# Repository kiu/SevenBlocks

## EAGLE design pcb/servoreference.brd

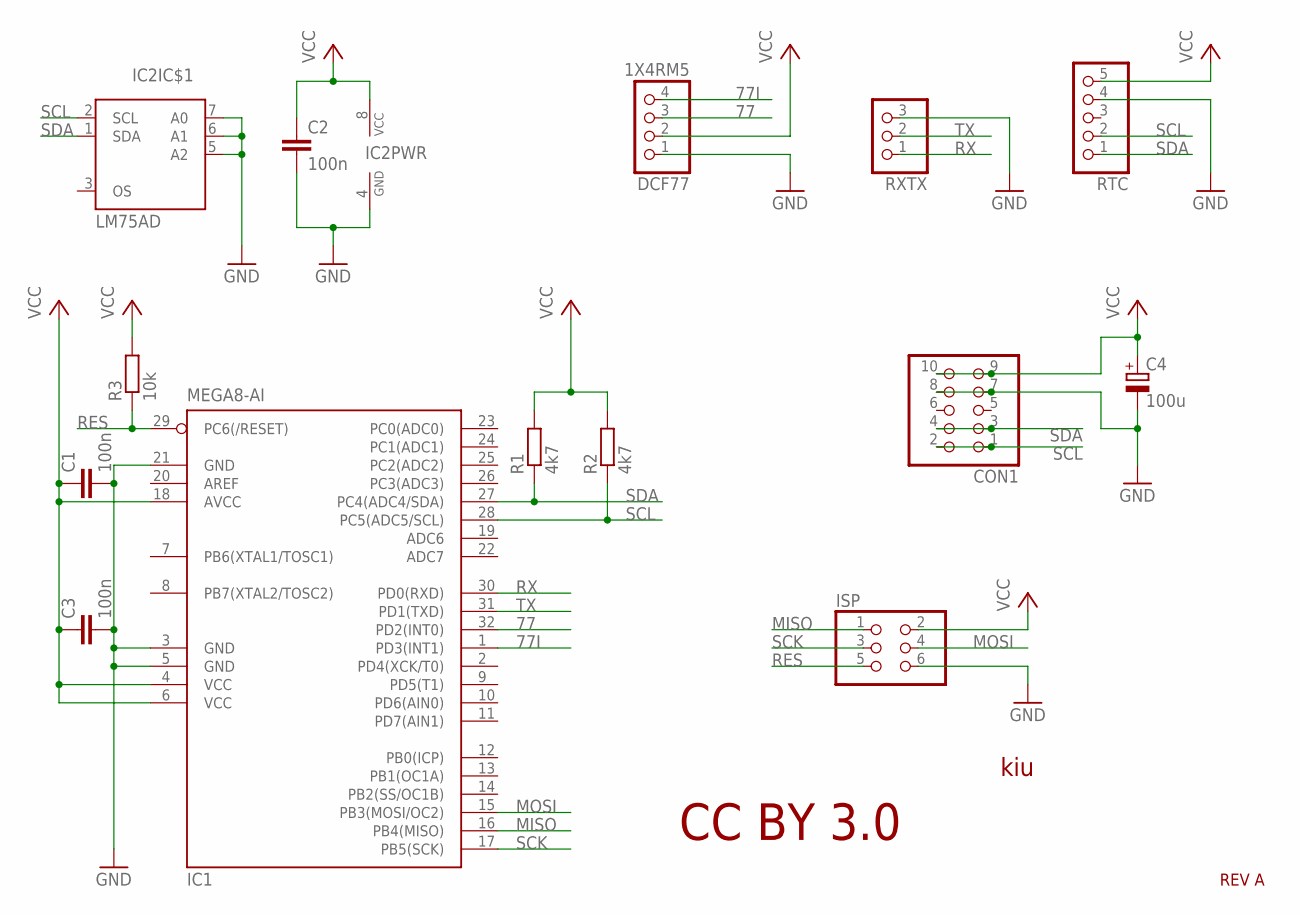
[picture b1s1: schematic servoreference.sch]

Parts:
C1, C2, C3: 100n; C0805
C4: 100u; 153CLV-0505
CON1: PINHD-2X5; 2X05
DCF77: 1X4RM5
IC1: MEGA8-AI; TQFP32-08; MPN ATMEGA8-16AU
IC2: LM75AD; SO08
ISP: PINHD-2X3; 2X03
R1, R2: 4k7; R0805
R3: 10k; R0805
RTC: PINHD-1X5; 1X05
RXTX: PINHD-1X3; 1X03

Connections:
77: DCF77.3, IC1.32 (PD2(INT0))
77I: DCF77.4, IC1.1 (PD3(INT1))
GND: C1.2, C2.2, C3.2, C4.-, CON1.7, CON1.8, DCF77.1, IC1.3 (GND), IC1.5 (GND), IC1.21 (GND), IC2.4 (GND), IC2.5 (A2), IC2.6 (A1), IC2.7 (A0), ISP.6, RTC.4, RXTX.3
MISO: IC1.16 (PB4(MISO)), ISP.1
MOSI: IC1.15 (PB3(MOSI/OC2)), ISP.4
RES: IC1.29 (PC6(/RESET)), ISP.5, R3.1
RX: IC1.30 (PD0(RXD)), RXTX.1
SCK: IC1.17 (PB5(SCK)), ISP.3
SCL: CON1.1, CON1.2, IC1.28 (PC5(ADC5/SCL)), IC2.2 (SCL), R2.1, RTC.2
SDA: CON1.3, CON1.4, IC1.27 (PC4(ADC4/SDA)), IC2.1 (SDA), R1.1, RTC.1
TX: IC1.31 (PD1(TXD)), RXTX.2
VCC: C1.1, C2.1, C3.1, C4.+, CON1.9, CON1.10, DCF77.2, IC1.4 (VCC), IC1.6 (VCC), IC1.18 (AVCC), IC2.8 (VCC), ISP.2, R1.2, R2.2, R3.2, RTC.5

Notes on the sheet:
CC BY 3.0
kiu
REV A

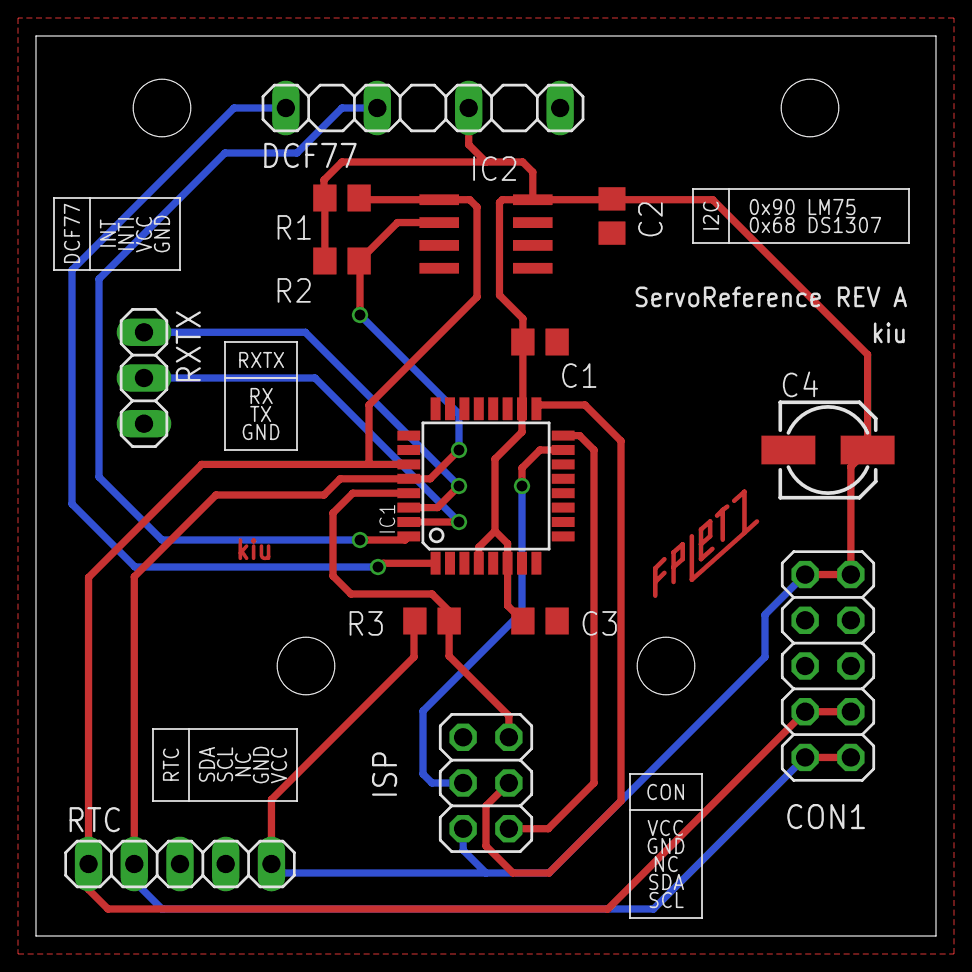
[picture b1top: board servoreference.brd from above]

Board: 2 copper layers, 50.0 x 50.0 mm, 14 parts (0 on the bottom side), 12 nets.

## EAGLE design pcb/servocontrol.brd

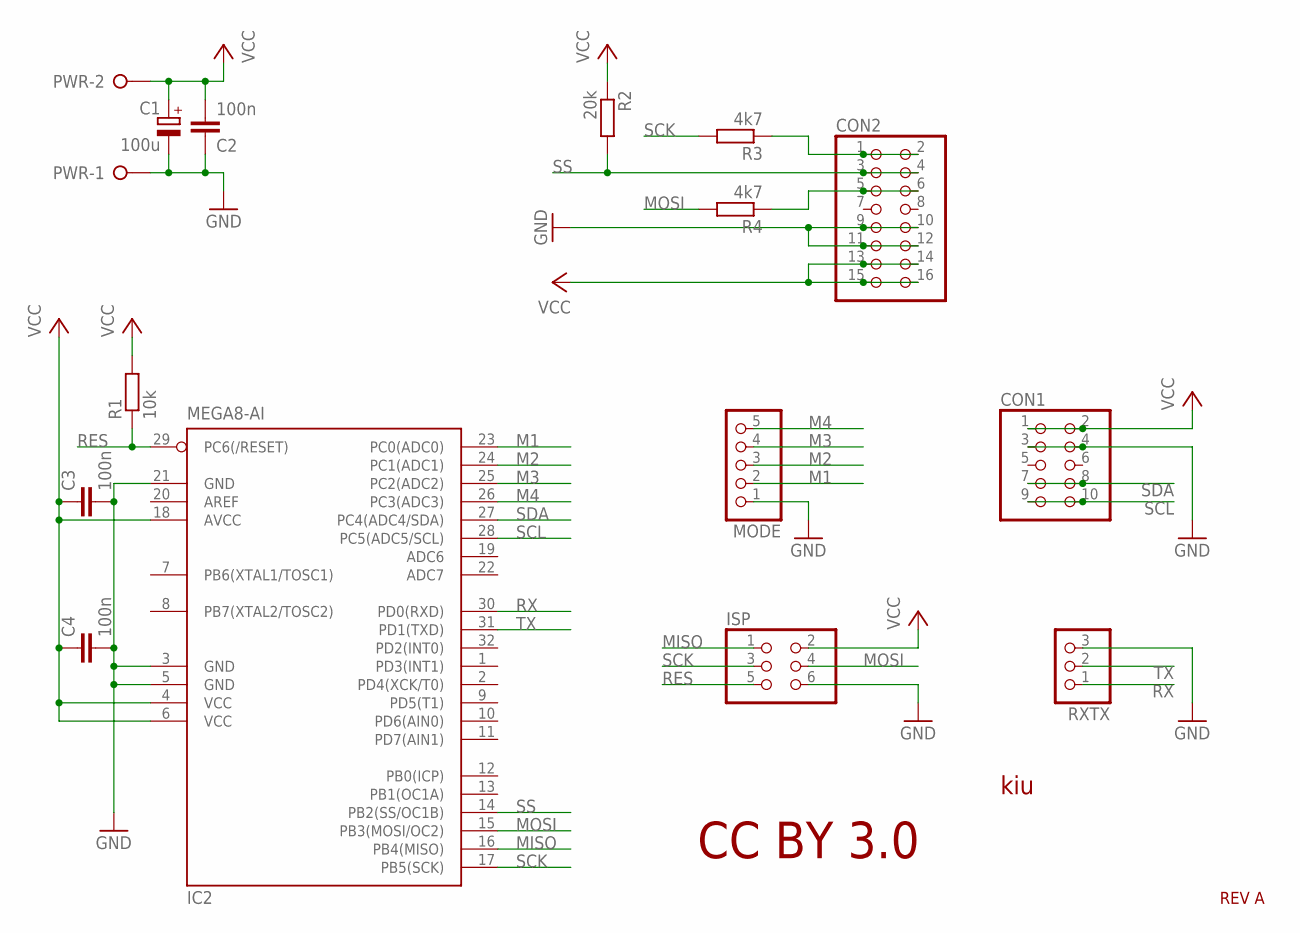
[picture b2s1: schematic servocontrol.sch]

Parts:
C1: 100u; 153CLV-0505
C2, C3, C4: 100n; C0805
CON1: PINHD-2X5; 2X05
CON2: PINHD-2X8; 2X08
IC2: MEGA8-AI; TQFP32-08; MPN ATMEGA8-16AU
ISP: PINHD-2X3; 2X03
MODE: PINHD-1X5; 1X05
PWR: W237-02P; W237-132
R1: 10k; R0805
R2: 20k; R0805
R3, R4: 4k7; R0805
RXTX: PINHD-1X3; 1X03

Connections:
GND: C1.-, C2.1, C3.2, C4.2, CON1.3, CON1.4, CON2.9, CON2.10, CON2.11, CON2.12, IC2.3 (GND), IC2.5 (GND), IC2.21 (GND), ISP.6, MODE.1, PWR.1, RXTX.3
M1: IC2.23 (PC0(ADC0)), MODE.2
M2: IC2.24 (PC1(ADC1)), MODE.3
M3: IC2.25 (PC2(ADC2)), MODE.4
M4: IC2.26 (PC3(ADC3)), MODE.5
MISO: IC2.16 (PB4(MISO)), ISP.1
MOSI: IC2.15 (PB3(MOSI/OC2)), ISP.4, R4.2
unnamed: CON2.5, CON2.6, R4.1
unnamed: CON2.1, CON2.2, R3.1
RES: IC2.29 (PC6(/RESET)), ISP.5, R1.1
RX: IC2.30 (PD0(RXD)), RXTX.1
SCK: IC2.17 (PB5(SCK)), ISP.3, R3.2
SCL: CON1.9, CON1.10, IC2.28 (PC5(ADC5/SCL))
SDA: CON1.7, CON1.8, IC2.27 (PC4(ADC4/SDA))
SS: CON2.3, CON2.4, IC2.14 (PB2(SS/OC1B)), R2.2
TX: IC2.31 (PD1(TXD)), RXTX.2
VCC: C1.+, C2.2, C3.1, C4.1, CON1.1, CON1.2, CON2.13, CON2.14, CON2.15, CON2.16, IC2.4 (VCC), IC2.6 (VCC), IC2.18 (AVCC), ISP.2, PWR.2, R1.2, R2.1

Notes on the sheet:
CC BY 3.0
kiu
REV A

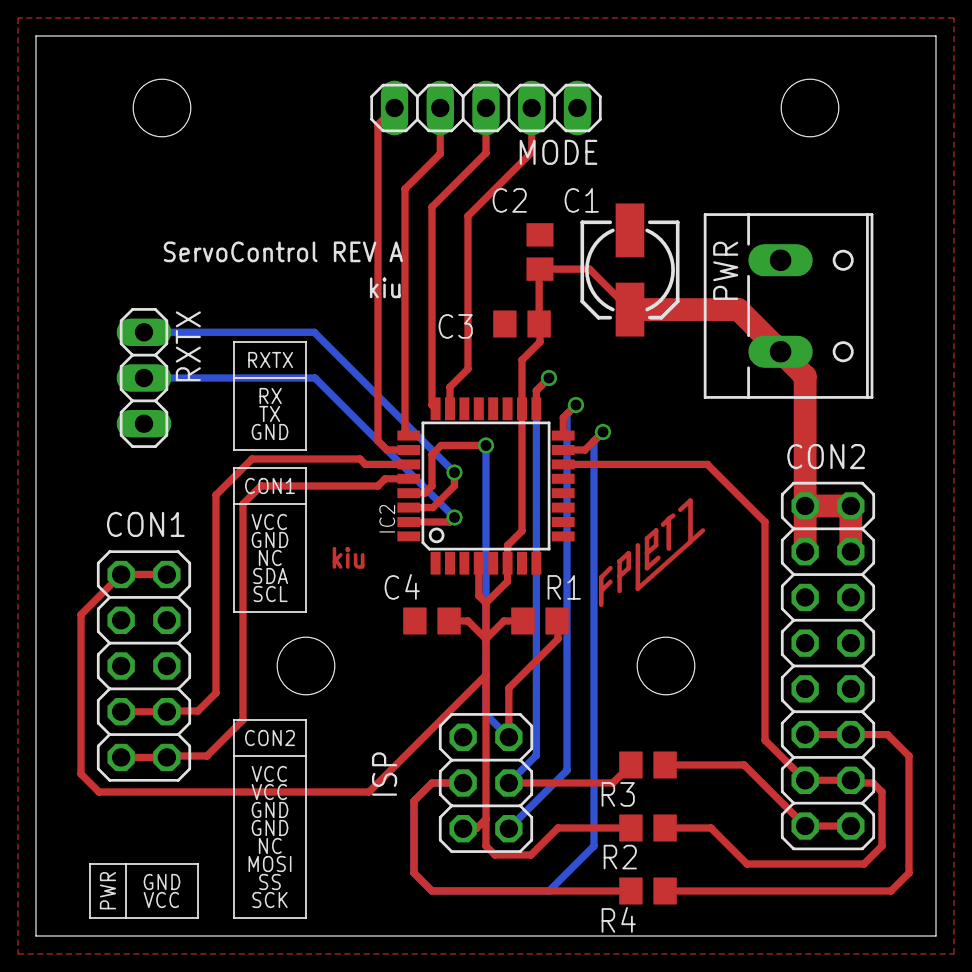
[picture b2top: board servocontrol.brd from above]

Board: 2 copper layers, 50.0 x 50.0 mm, 15 parts (0 on the bottom side), 17 nets.

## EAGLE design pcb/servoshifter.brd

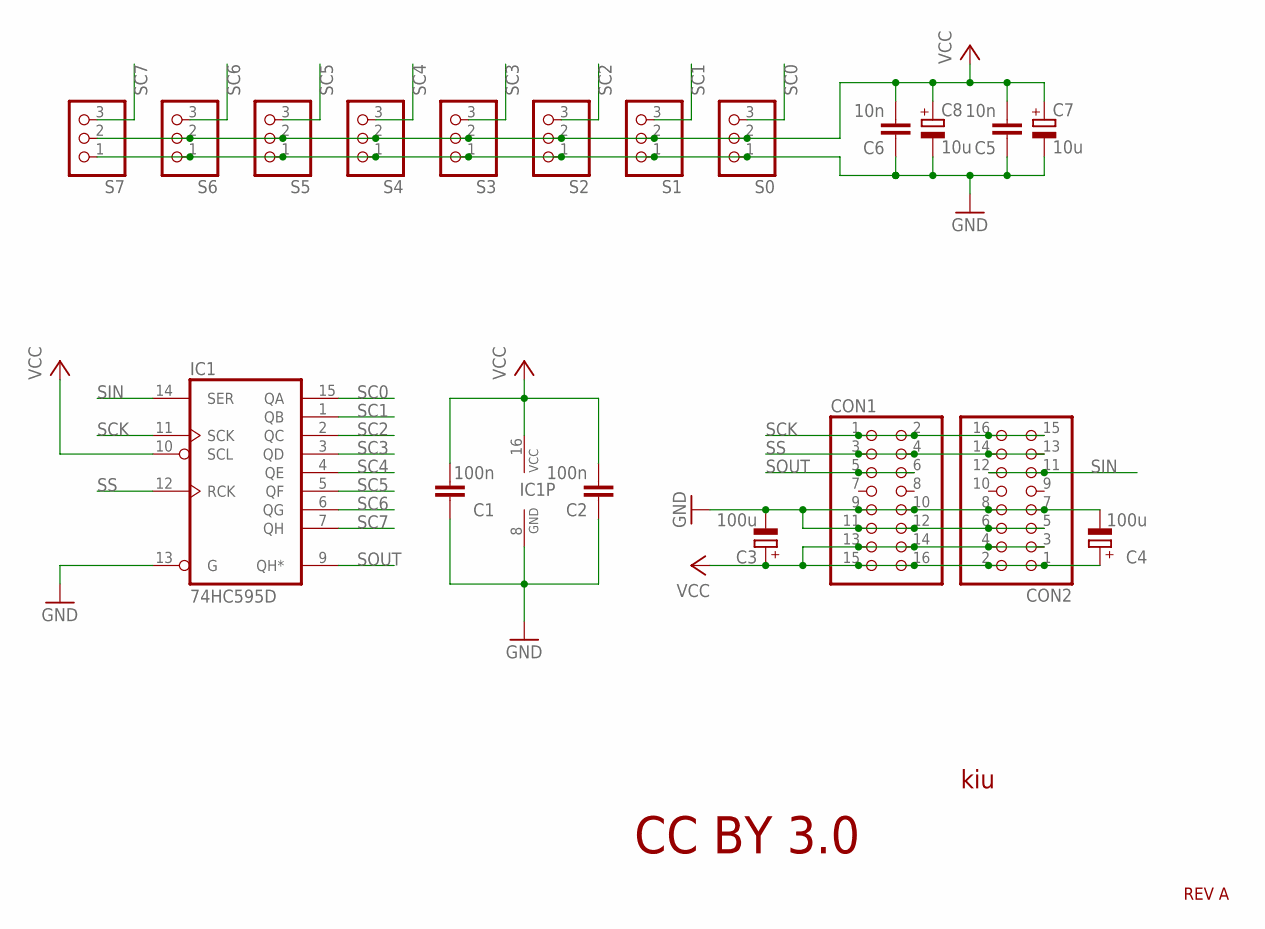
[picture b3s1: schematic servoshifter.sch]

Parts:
C1, C2: 100n; C0805
C3, C4: 100u; 153CLV-0505
C5, C6: 10n; C0805
C7, C8: 10u; 153CLV-0405
CON1, CON2: PINHD-2X8; 2X08
IC1: 74HC595D; SO16
S0, S1, S2, S3, S4, S5, S6, S7: PINHD-1X3; 1X03

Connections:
GND: C1.1, C2.1, C3.-, C4.-, C5.1, C6.1, C7.-, C8.-, CON1.9, CON1.10, CON1.11, CON1.12, CON2.5, CON2.6, CON2.7, CON2.8, IC1.8 (GND), IC1.13 (G), S0.1, S1.1, S2.1, S3.1, S4.1, S5.1, S6.1, S7.1
SC0: IC1.15 (QA), S0.3
SC1: IC1.1 (QB), S1.3
SC2: IC1.2 (QC), S2.3
SC3: IC1.3 (QD), S3.3
SC4: IC1.4 (QE), S4.3
SC5: IC1.5 (QF), S5.3
SC6: IC1.6 (QG), S6.3
SC7: IC1.7 (QH), S7.3
SCK: CON1.1, CON1.2, CON2.15, CON2.16, IC1.11 (SCK)
SIN: CON2.11, CON2.12, IC1.14 (SER)
SOUT: CON1.5, CON1.6, IC1.9 (QH*)
SS: CON1.3, CON1.4, CON2.13, CON2.14, IC1.12 (RCK)
VCC: C1.2, C2.2, C3.+, C4.+, C5.2, C6.2, C7.+, C8.+, CON1.13, CON1.14, CON1.15, CON1.16, CON2.1, CON2.2, CON2.3, CON2.4, IC1.10 (SCL), IC1.16 (VCC), S0.2, S1.2, S2.2, S3.2, S4.2, S5.2, S6.2, S7.2

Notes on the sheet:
CC BY 3.0
kiu
REV A

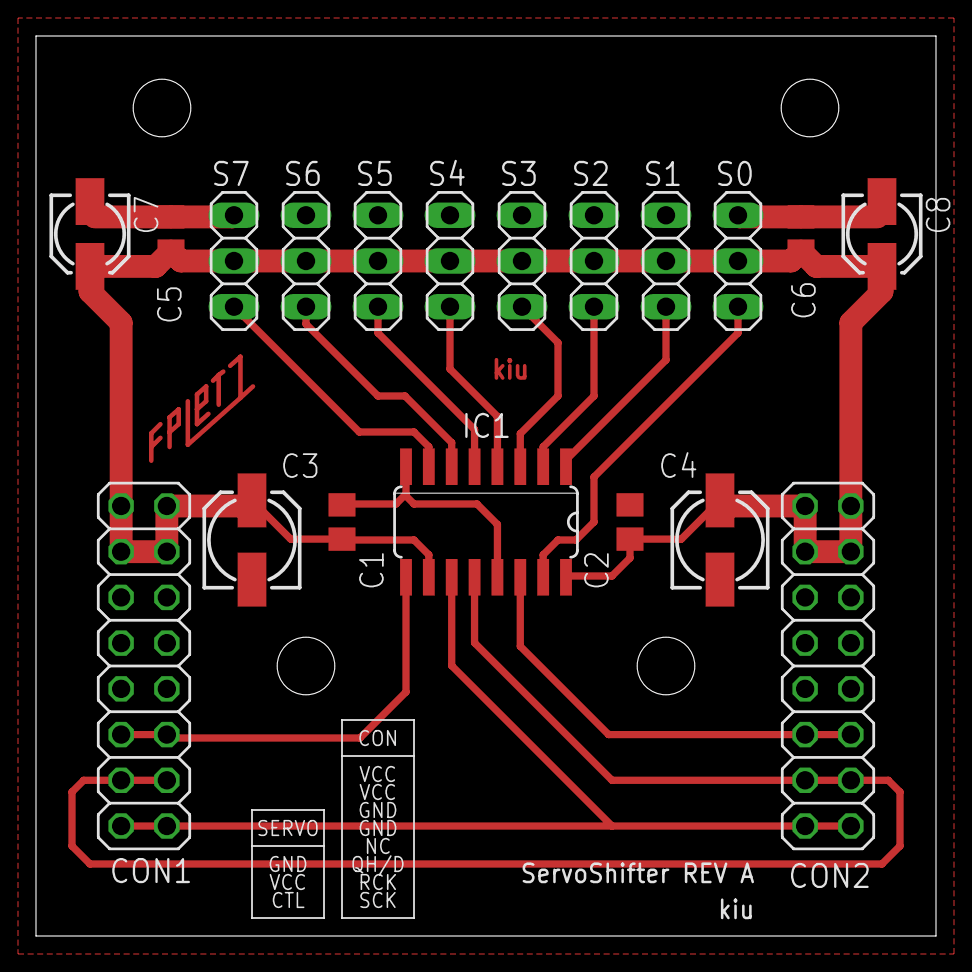
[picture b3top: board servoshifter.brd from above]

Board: 2 copper layers, 50.0 x 50.0 mm, 19 parts (0 on the bottom side), 14 nets.

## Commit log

2012-04-07 Initial project release
